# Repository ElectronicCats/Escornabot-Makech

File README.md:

View this project on [CADLAB.io](https://cadlab.io/project/1721). 

# Escornabot Makech

**[OSHW] MX000009 | Certified open source hardware |** [oshwa.org/cert.](https://www.oshwa.org/cert)

Escornabot es un proyecto de código/hardware abierto cuyo objetivo es acercar la robótica y la programación a los niños y niñas.

El Escornabot básico puede programarse con los botones para ejecutar secuencias de movimientos. A partir de aquí, la imaginación es el único límite en las posibilidades.

## Makech
Diseño de robot basado en el Escornabot Ogaki, creado con el microcontrolador SAMD21 Cortex M0 de 32 bits completamente hecho en KiCAD, especialmente creado para enseñar programación con Arduino, MakeCode y CircuitPython.

Al tener todos los circuitos integrados, elimina la necesidad de cablear, minimizando los errores de electrónica, lo que conlleva un incremento en el tiempo dedicado a programación y al conocimiento de nuevos lenguajes de programación.

Con amor para todo el mundo desde Aguascalientes - México.

- Consigue tu kit, visita: [https://electroniccats.com](https://electroniccats.com)

## Ogaki

Diseño de robot basado en el Escornabot, completamente hecho en KiCAD. 

Con amor para todo el mundo desde Malmo - Suecia.

# Créditos

- Escorna CPU 2.20 by [Xdesig](https://github.com/xdesig)

- Los creadores originales de [Escornabot](www.escornabot.com), su comunidad de usuarios y desarrolladores 

# Autor

**Makech - Andrés Sabas and Joe at Electronic Cats**

_Electronic Cats es una empresa de hardware libre hecho en México_

**Ogaki - J. Garcia at abierto.cc**

_Abierto es una inciativa de D. Cuartielles gracias a la generosa aportación de la Fundación PUIG por intermediación de la Fundación Ashoka de cara a contribuir a la creación de material educativo de libre acceso y circulación_

**Escorna CPU 2.20 - XDESIG**

_Nature's walking, Percorrendo a Natureza. Deseñando Electrónica_

# License

Attribution-ShareAlike 4.0 International (CC BY-SA 4.0)
 
Makech - Designed by Electronic Cats.

Hardware released under an CERN Open Hardware Licence v1.2. See the LICENSE_HARDWARE file for more information.

Electronic Cats is a registered trademark, please do not use if you sell these PCBs.

3 Mar 2019

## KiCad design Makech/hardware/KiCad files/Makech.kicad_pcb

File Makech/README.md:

# Escornabot Makech

Diseño de robot basado en el Escornabot Ogaki, creado con el microcontrolador SAMD21 Cortex M0 de 32 bits completamente hecho en KiCAD, especialmente creado para enseñar programación con Arduino, MakeCode y CircuitPython.

Al tener todos los circuitos integrados, elimina la necesidad de cablear, minimizando los errores de electrónica, lo que conlleva un incremento en el tiempo dedicado a programación y al conocimiento de nuevos lenguajes de programación.
Con amor para todo el mundo desde Aguascalientes - México.

# Consigue tu kit

Si quieres conseguir el kit para montarlo, visita: [https://electroniccats.com](https://electroniccats.com)

# Instrucciones de montaje

Puedes ver las instrucciones de montaje paso a paso en:

# Créditos

Los creadores originales de Escornabot y su comunidad de usuarios y desarrolladores

# Autor

Makech - Andrés Sabas at Electronic Cats

# Electronic Cats

Electronic Cats es una hardware libre hecho en México

Makech - Designed by Electronic Cats.

Hardware released under an CERN Open Hardware Licence v1.2. See the LICENSE_HARDWARE file for more information.

Electronic Cats is a registered trademark, please do not use if you sell these PCBs.

3 Mar 2019

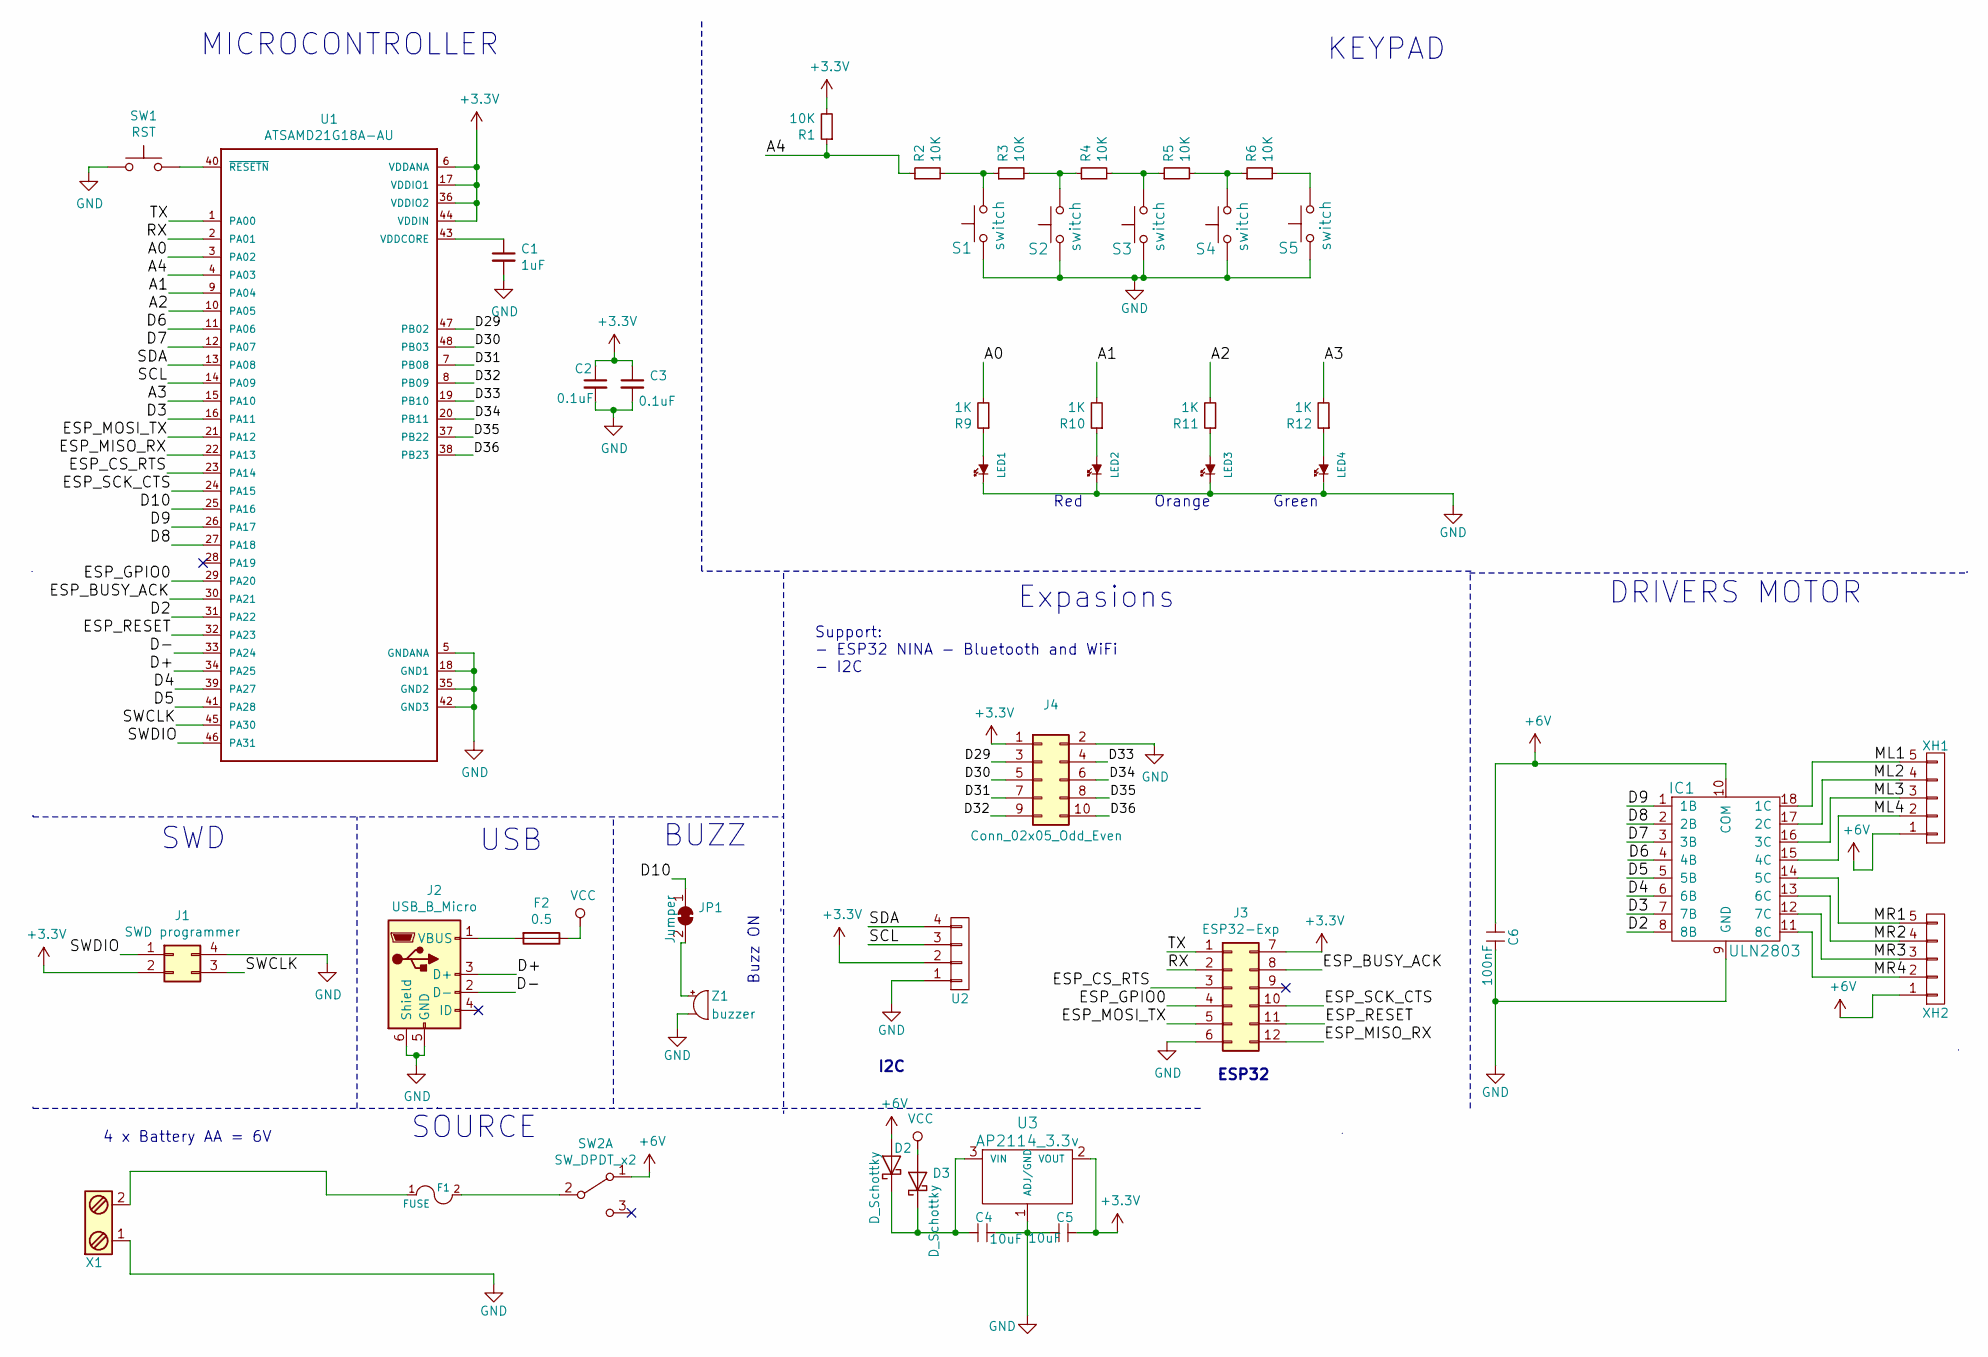
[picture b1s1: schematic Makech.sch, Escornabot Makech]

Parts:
C1: 1uF; C_0805_2012Metric_Pad1.15x1.40mm_HandSolder
C2, C3: 0.1uF; C_0805_2012Metric_Pad1.15x1.40mm_HandSolder
C4: 10uF; C_0805_2012Metric_Pad1.15x1.40mm_HandSolder
C5: 10uF; C_0805_2012Metric
C6: 100nF; C_0805_2012Metric_Pad1.15x1.40mm_HandSolder
D2, D3: D_Schottky; D_SOD-123
F1: FUSE; R_1812_HandSoldering
F2: 0.5; R_1812_HandSoldering
IC1: ULN2803; SOIC-18W_7.5x11.6mm_P1.27mm
J1: SWD programmer; 621X04245821
J2: USB_B_Micro; U254051N4BH806
J3: ESP32-Exp; 610X1221121
J4: Conn_02x05_Odd_Even; PinHeader_2x05_P2.54mm_Vertical
JP1: Jumper; SolderJumper-2_P1.3mm_Bridged_RoundedPad1.0x1.5mm
LED1, LED2, LED3, LED4: L; LED_D3.0mm
R1, R2, R3, R4, R5, R6: 10K; R_0805_2012Metric_Pad1.15x1.40mm_HandSolder
R9, R10, R11, R12: 1K; R_0805_2012Metric_Pad1.15x1.40mm_HandSolder
S1, S2, S3, S4, S5: switch; SW_PUSH-12mm_Wuerth-430476085716
SW1: RST; SW_SPST_TL3342
SW2: SW_DPDT_x2; SW_CuK_OS102011MA1QN1_SPDT_Angled
U1: ATSAMD21G18A-AU; TQFP-48_7x7mm_P0.5mm
U2: CONN_01X04; PinHeader_1x04_P2.54mm_Vertical
U3: AP2114_3.3v; SOT-223
X1: Screw_Terminal_1x02; TerminalBlock_bornier-2_P5.08mm
XH1, XH2: CONN_01X05; Molex_KK-254_AE-6410-05A_1x05_P2.54mm_Vertical
Z1: buzzer; MagneticBuzzer_ProSignal_ABI-009-RC

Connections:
+3V3: C2.1, C3.1, C5.1, J1.2, J3.7, J4.1, R1.2, U1.6 (VDDANA), U1.17 (VDDIO1), U1.36 (VDDIO2), U1.44 (VDDIN), U2.2, U3.2 (VOUT)
+6V: C6.2, D2.2 (A), IC1.10 (COM), SW2.1 (A), XH1.1, XH2.1
/A0: R9.2, U1.3 (PA02)
/A1: R10.2, U1.9 (PA04)
/A2: R11.2, U1.10 (PA05)
/A3: R12.2, U1.15 (PA10)
/A4: R1.1, R2.1, U1.4 (PA03)
/D2: IC1.8 (8B), U1.31 (PA22)
/D3: IC1.7 (7B), U1.16 (PA11)
/D4: IC1.6 (6B), U1.39 (PA27)
/D5: IC1.5 (5B), U1.41 (PA28)
/D6: IC1.4 (4B), U1.11 (PA06)
/D7: IC1.3 (3B), U1.12 (PA07)
/D8: IC1.2 (2B), U1.27 (PA18)
/D9: IC1.1 (1B), U1.26 (PA17)
/D10: JP1.1 (A), U1.25 (PA16)
/D29: J4.3, U1.47 (PB02)
/D30: J4.5, U1.48 (PB03)
/D31: J4.7, U1.7 (PB08)
/D32: J4.9, U1.8 (PB09)
/D33: J4.4, U1.19 (PB10)
/D34: J4.6, U1.20 (PB11)
/D35: J4.8, U1.37 (PB22)
/D36: J4.10, U1.38 (PB23)
/D+: J2.3 (D+), U1.34 (PA25)
/D-: J2.2 (D-), U1.33 (PA24)
/ESP_BUSY_ACK: J3.8, U1.30 (PA21)
/ESP_CS_RTS: J3.3, U1.23 (PA14)
/ESP_GPIO0: J3.4, U1.29 (PA20)
/ESP_MISO_RX: J3.12, U1.22 (PA13)
/ESP_MOSI_TX: J3.5, U1.21 (PA12)
/ESP_RESET: J3.11, U1.32 (PA23)
/ESP_SCK_CTS: J3.10, U1.24 (PA15)
/ML1: IC1.18 (1C), XH1.5
/ML2: IC1.17 (2C), XH1.4
/ML3: IC1.16 (3C), XH1.3
/ML4: IC1.15 (4C), XH1.2
/MR1: IC1.14 (5C), XH2.5
/MR2: IC1.13 (6C), XH2.4
/MR3: IC1.12 (7C), XH2.3
/MR4: IC1.11 (8C), XH2.2
/RX: J3.2, U1.2 (PA01)
/SCL: U1.14 (PA09), U2.3
/SDA: U1.13 (PA08), U2.4
/SWCLK: J1.3, U1.45 (PA30)
/SWDIO: J1.1, U1.46 (PA31)
/TX: J3.1, U1.1 (PA00)
GND: C1.2, C2.2, C3.2, C4.1, C5.2, C6.1, IC1.9 (GND), J1.4, J2.5 (GND), J2.6 (Shield), J3.6, J4.2, LED1.1 (K), LED2.1 (K), LED3.1 (K), LED4.1 (K), S1.1, S2.1, S3.1, S4.1, S5.1, SW1.1, U1.5 (GNDANA), U1.18 (GND1), U1.35 (GND2), U1.42 (GND3), U2.1, U3.1 (ADJ/GND), X1.1, Z1.2
unnamed: C1.1, U1.43 (VDDCORE)
unnamed: C4.2, D2.1 (K), D3.1 (K), U3.3 (VIN)
unnamed: F1.2, SW2.2 (B)
unnamed: F1.1, X1.2
unnamed: F2.2, J2.1 (VBUS)
unnamed: JP1.2 (B), Z1.1
unnamed: LED1.2 (A), R9.1
unnamed: LED2.2 (A), R10.1
unnamed: LED3.2 (A), R11.1
unnamed: LED4.2 (A), R12.1
unnamed: R2.2, R3.1, S1.2
unnamed: R3.2, R4.1, S2.2
unnamed: R4.2, R5.1, S3.2
unnamed: R5.2, R6.1, S4.2
unnamed: R6.2, S5.2
unnamed: SW1.2, U1.40 (~RESETN~)
VCC: D3.2 (A), F2.1

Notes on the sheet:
KEYPAD
BUZZ
Buzz ON
I2C
Expasions
Red
Orange
Green
4 x Battery AA = 6V
MICROCONTROLLER
Support: - ESP32 NINA - Bluetooth and WiFi - I2C
DRIVERS MOTOR
USB
SWD
ESP32
SOURCE

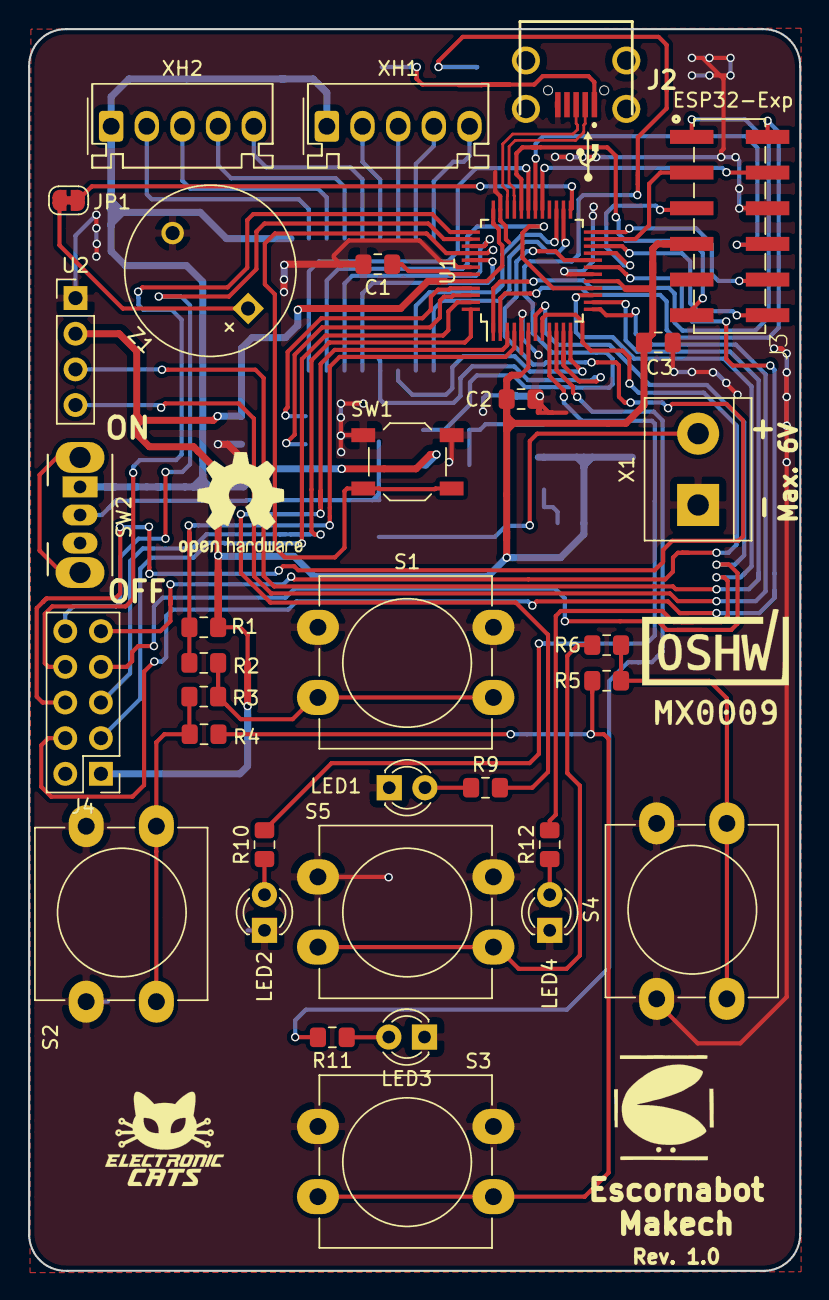
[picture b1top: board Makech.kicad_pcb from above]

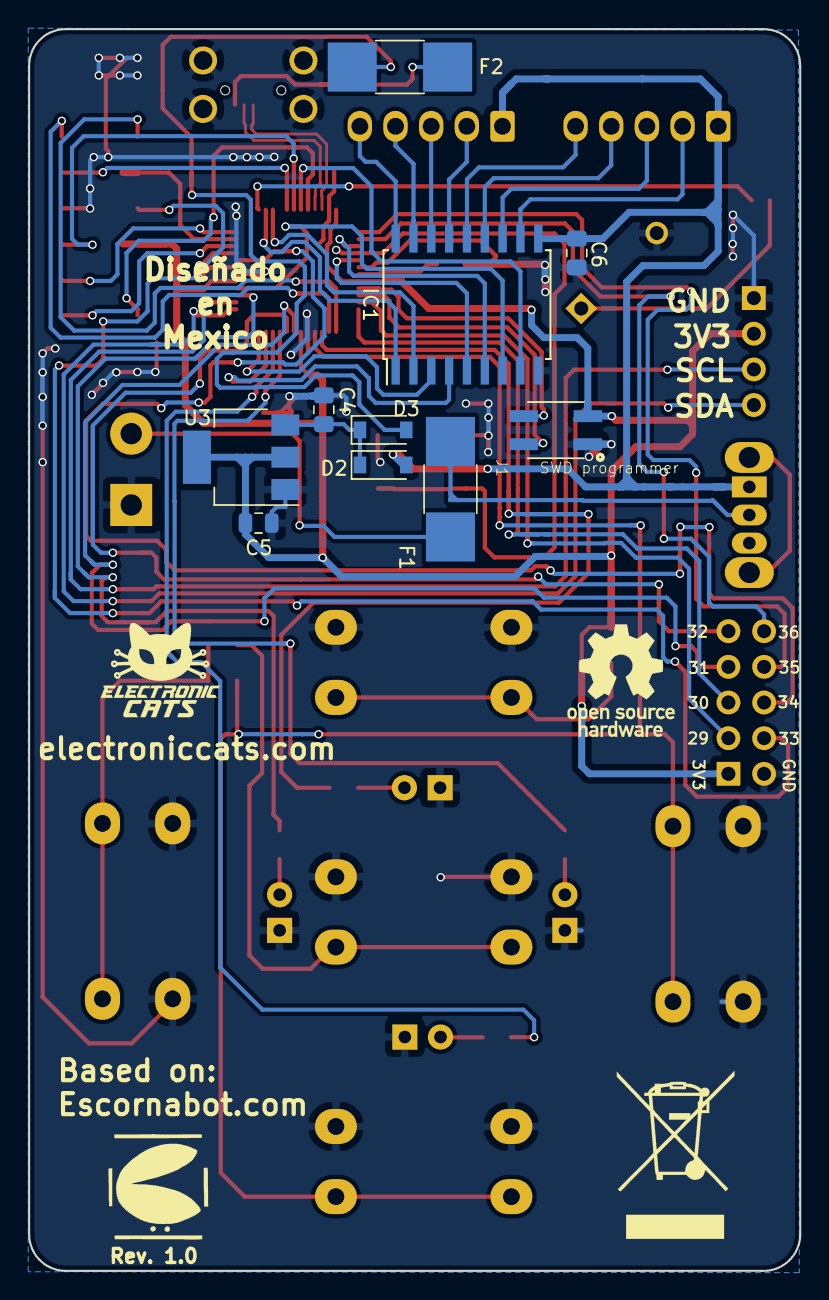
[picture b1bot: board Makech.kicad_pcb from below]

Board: 2 copper layers, 54.9 x 88.5 mm, 45 parts (10 on the bottom side), 65 nets.

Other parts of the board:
svg2mod: G***; usb_graphic

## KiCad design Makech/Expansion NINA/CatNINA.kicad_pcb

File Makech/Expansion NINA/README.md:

# Upgrade All-in-One ESP32 Firmware

## Uploading Serial Passthrough Code

Lo primero que se debe realizar es instalar la biblioteca "WiFiNINA" en el arduino library manager y cargar al Escornabot el ejemplo **"Serial Passthrough"**, una vez terminada la carga del firmware continue en el siguiente paso

## Subiendo nina-fw con esptool

¡Esta sección asume que usted sabe cómo usar 'esptool' para cargar firmware a su ESP! Si no está seguro, consulte https://github.com/espressif/esptool y busque tutoriales.
Haga clic en el siguiente enlace para descargar el último archivo .bin de nina-fw. Descomprimir que y guardar el archivo .bin a su escritorio .

Si está utilizando macOS o Linux , ejecute el siguiente comando, reemplazándolo /dev/ttys6con el puerto serie de su placa y  NINA_W102-1.3.0con el archivo binario que está actualizando al ESP32.

esptool.py --port /dev/ttyS6 --before no_reset --baud 115200 write_flash 0 NINA_W102-1.3.0.bin

Si está utilizando Windows , ejecute el siguiente comando, reemplazándolo COM7con el puerto serie de su placa y  NINA_W102-1.3.0con el archivo binario que está actualizando al ESP32

esptool.py --port COM7 --before no_reset --baud 115200 write_flash 0 NINA_W102-1.3.0.bin

El comando debería detectar el ESP32 y tardará uno o dos minutos en cargar el firmware. El NeoPixel en su placa parpadeará y parpadeará a medida que se carga el firmware. 

Si ESPTool no detecta el ESP32 , asegúrese de haber subido el archivo .UF2 correcto al gestor de arranque.

Una vez que el firmware está completamente cargado, el ESP32 se reiniciará y el NeoPixel se iluminará en azul. 

## Verificación de la versión de firmware actualizada

Para verificar que todo funcione correctamente, cargaremos un boceto Arduino o un código CircuitPython. 

Si anteriormente estaba usando su ESP32 con Arduino, debe cargar un boceto de Arduino para verificar que todo funcione correctamente y que la versión del nina-fw se correlaciona con la versión que lee el boceto.

Abra Archivo-> Ejemplos-> WiFiNINA-> ScanNetworks y cargue el boceto. Luego, abra el Monitor de serie. Debería ver la versión del firmware impresa en el monitor serie.

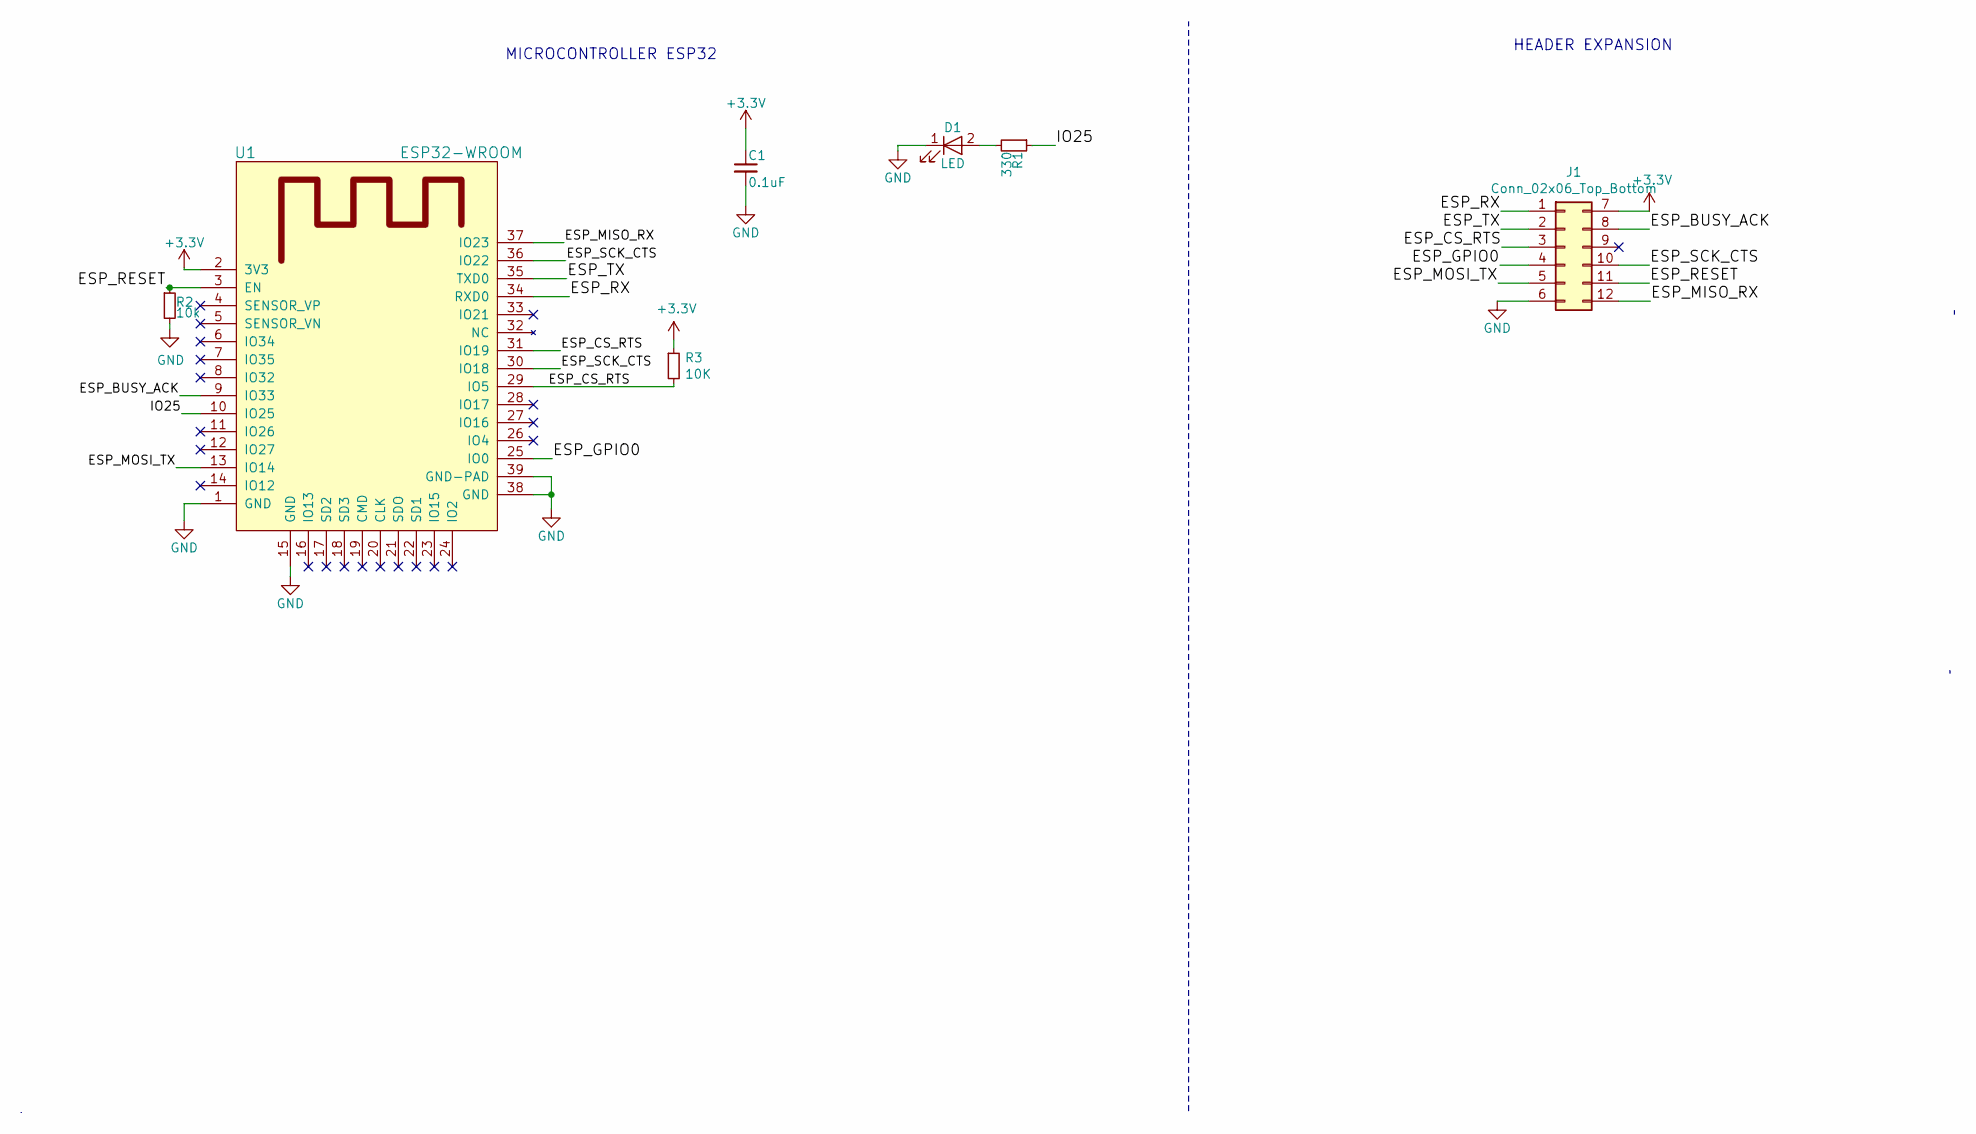
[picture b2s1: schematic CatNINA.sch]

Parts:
C1: 0.1uF; C_0805_HandSoldering
D1: LED; LED_0805_HandSoldering
J1: Conn_02x06_Top_Bottom; 61301221121
R1: 330; R_0805_HandSoldering
R2: 10k; R_0805_HandSoldering
R3: 10K; R_0805_HandSoldering
U1: ESP32-WROOM

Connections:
+3V3: C1.1, J1.7, R3.1, U1.2 (3V3)
/ESP_BUSY_ACK: J1.8, U1.9 (IO33)
/ESP_CS_RTS: J1.3, R3.2, U1.29 (IO5), U1.31 (IO19)
/ESP_GPIO0: J1.4, U1.25 (IO0)
/ESP_MISO_RX: J1.12, U1.37 (IO23)
/ESP_MOSI_TX: J1.5, U1.13 (IO14)
/ESP_RESET: J1.11, R2.1, U1.3 (EN)
/ESP_RX: J1.1, U1.34 (RXD0)
/ESP_SCK_CTS: J1.10, U1.30 (IO18), U1.36 (IO22)
/ESP_TX: J1.2, U1.35 (TXD0)
/IO25: R1.1, U1.10 (IO25)
GND: C1.2, D1.1 (K), J1.6, R2.2, U1.1 (GND), U1.15 (GND), U1.38 (GND), U1.39 (GND-PAD)
unnamed: D1.2 (A), R1.2

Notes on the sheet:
MICROCONTROLLER ESP32
HEADER EXPANSION

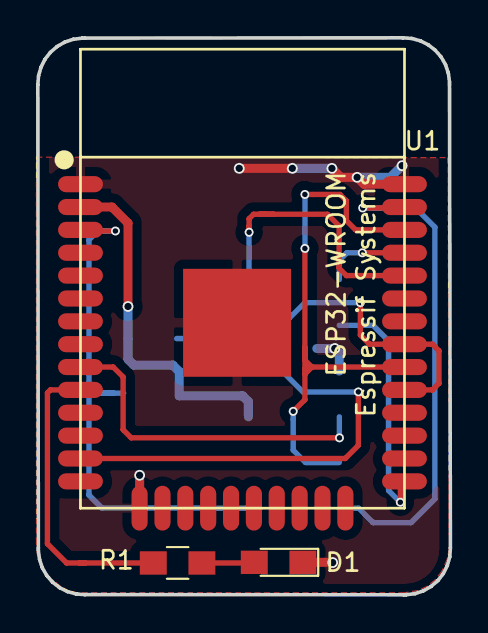
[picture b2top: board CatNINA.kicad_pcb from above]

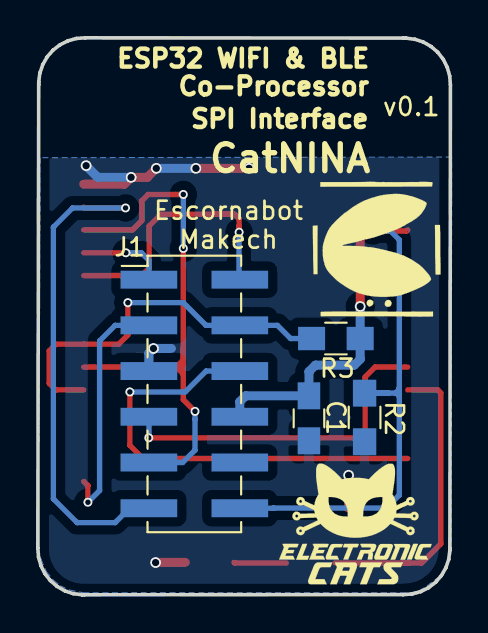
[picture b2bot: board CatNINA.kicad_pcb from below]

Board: 2 copper layers, 22.9 x 30.9 mm, 7 parts (4 on the bottom side), 13 nets.

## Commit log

2019-02-10 kicad init
2019-02-10 model 3d thanks Ogaki
2019-02-10 update README de Makech
2019-02-10 update README 3d
2019-02-10 fix README
2019-02-10 Init firmware compatible SAMD21
2019-02-10 silks
2019-02-10 clean pcb for new desing
2019-02-10 init select footprint
2019-02-10 add usb description
2019-02-25 init BOM
2019-02-27 Header ESP32 Expansion
2019-02-28 BOM complete
2019-03-01 Update autors CC
    Thanks escornabot.com, Pablo Rubio, XDeSIG and abierto.cc
2019-03-02 migrate to SAMD21G18
2019-03-04 update v0.2
    migrate to SAMD21G
2019-03-04 assign pins
2019-03-04 SPI for ESP32
2019-03-04 Eliminate unnecessary elements
2019-03-04 Schematic v0.2
2019-03-04 remove furubot without support
2019-03-04 Update README Maketch
2019-03-04 Update README, remove furubot
2019-03-04 Create LICENSE_HARDWARE
2019-03-09 Fix error library index
2019-03-09 remove components x.1
2019-03-09 add recue.lib
2019-03-09 cache lib
2019-03-12 FOOTPRINT
2019-03-15 Footprint complet
2019-03-19 Complete
2019-03-19 USB correct
2019-03-23 pre router
2019-03-23 update silk
2019-03-24 change leds 3mm
2019-03-24 remove jumper extra and capacitors
2019-03-24 Fix source motors
2019-03-24 fix source motor pcb
2019-03-24 add logo
2019-03-24 add credits
2019-03-24 add symbol jumper
2019-03-24 update labels
2019-03-26 fix pcb
2019-03-26 fix2 pcb
2019-03-26 capacitors sources
2019-03-27 pistas
2019-03-28 PCB COMPLETE
2019-03-28 v0.1
2019-03-29 update Silks
2019-03-29 foot-print change
2019-04-04 Create LICENSE
2019-04-16 Update firmware version 2019
2019-04-29 Re-define pins for Arduino and Makecode in Schematic
2019-04-29 Update Description
2019-04-29 Schematic PDF
2019-04-29 Add OSHWA-MX009!
2019-04-29 Change connector ESP32, SWD and logo OSWHA
2019-04-29 Backlink to CADLAB.io has been added.
2019-04-30 rename path
2019-04-30 add bootloader uf2 files
2019-05-03 firmware default uf2
2019-05-10 update value for button
2019-05-11 change terminal block
2019-05-11 Change routing and compnent placement v0.2
2019-05-11 Fix traces
2019-05-11 Fix clearance and GND traces
2019-05-11 Clearance gnd bottom fix
2019-05-14 Change Fusible and add conector expansion
2019-05-15 Fix edge cuts mm
2019-05-17 route digital outputs and fusibes
2019-05-28 init CatNINA
2019-05-28 Init PCB and netlist
2019-05-29 size in margin
2019-05-29 update schematic
2019-05-29 Fix Line and Turn steps
    Thanks @ForeverWero
2019-05-30 routeo NINA
2019-06-03 model 3D CatNiNA
2019-06-03 init example
2019-06-03 Simple test commands
2019-06-03 fix text escornabot
2019-06-03 move connector
2019-06-03 .step nina
2019-06-03 routeo moved connector
2019-06-03 actualization .step NINA
2019-06-03 mesures
2019-06-04 update working
2019-06-04 change mesure layer
2019-06-04 debug define in example
2019-06-04 init add module CatNINA
2019-06-05 add man # to connector
2019-06-06 Fix error NINA_RESET to GND
2019-06-06 change TX and RX
2019-06-06 move conector
2019-06-07 pin reset move of gnd
2019-06-10 CS fix voltage
2019-06-11 Remove CS tracks to voltage
2019-06-11 Update connector to 2.54mm and fix traces and ground plane
2019-06-19 Update traces fix ground missed
2019-07-17 new calibration for new case
2019-07-18 escornabot plug and play version
2019-07-18 Fix path and names
2019-08-14 change values configuration
2019-08-14 update v3
2019-08-14 update BOM
2019-08-14 update image
2019-10-17 update firmware CatNINA
2019-10-17 images
2019-10-17 Rename Upgrade All-in-One ESP32.md to README.md
2019-10-20 Init fix connection for BLE
2019-10-20 init cat nina support BLE
2019-10-20 rename mosi and miso
2019-10-20 remove not connect lines
2019-10-29 Update vias
2019-10-29 brush traces
2019-10-29 update traces WiFiNINA
2019-10-29 Add footprint to local library erase track
2020-01-10 update firmware default for restore
2020-01-10 add bin
2020-02-26 remove Diode zener innecesary
